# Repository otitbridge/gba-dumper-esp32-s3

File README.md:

# GBAダンパー — バイナリ配布

**導入済みの評価機を受け取った方へ：** [受取後の接続・初回Wi-Fi・ROM／セーブ操作・GBA実機での確認](EVALUATION.md)から始めてください。FW書込みは不要です。機器Wi-Fiの接続情報は譲渡元から個別にお渡しします。

**iPhoneの「ファイル」でROMを取り出し、ファームウェア更新もブラウザから。**
GBAカートリッジのバックアップを、スマホから使いやすく。これから始める人の「入門用の1台目」を目指しています。

- **USBケーブル1本でROMをコピー。** ネイティブUSBに接続すると「GBA-DUMPER」が表示され、iPhoneの「ファイル」やPCから取り出せます。Wi-Fi設定は不要です。
- **Wi-Fiではブラウザから操作。** ROMの読み出し・保存、対応するセーブデータのバックアップ・書込み・元データへの復元ができます。専用アプリのインストールは不要です。
- **更新のためにPCへつなぎ直す手間を減らす。** 初回導入・接続設定後は、ブラウザでGitHubの最新版を確認して更新できます。端末へ保存した署名付き更新ファイルを選ぶ方法にも対応します。
- **更新後の確認と、戻すためのしくみ。** 正規の更新ファイルかを署名で検証し、更新後に起動を確定できなければ旧版へ戻ります。有線書込みによる復旧経路も維持しています。

**ROM 4容量・セーブ5構成で実機検証済み。対応タイトルではWebから自動設定。**

ROMは4／8／16／32 MiB、セーブはEEPROM 512 B／8 KiB、SRAM・FRAM互換32 KiB、Flash 64／128 KiBを確認しています。対応範囲は確認済みタイトル・Rev・チップに限ります。0.25.4は64 KiB Flash対応を含みます。これらは各開発段階の実績で、今回の配布アプリそのものの確認範囲は[検証状況](VALIDATION.md)を参照してください。

[使い方とセーブの復元](USAGE.md) ／ [ファームウェア更新](UPDATE.md) ／ [FW書込み・有線復旧（開発／保守向け）](INSTALL.md)

画像は利用方法を伝える説明用イメージです。[開発の様子をXで見る](https://x.com/ot_it_bridge/status/2111419544761925654)

WeAct ESP32S3-A N16R2と本プロジェクトのGBA用基板V1（20260928）向けの開発版ファームウェアです。
この配布物は **0.25.4 / public build**。ソースコード・最新の設計ファイルは配布しません。GitHubは書込み用バイナリ、操作説明、不具合報告の窓口として使用します。

0.25.4は、Web画面を「USB／Web切替」「ROM読み出し」「セーブ読み書き」「ファームウェア更新」の4タブへ整理しました。Web操作の接続・切断とWi-Fi設定は上部の共通欄にまとめ、Web・Wi-Fi・USBの状態を区別します。タブを移動しても処理と元バックアップを保持し、必要な復元を共通警告で案内します。

前回公開0.22.4から、赤の救助隊国内版B24J Rev0・実物ID D4BFのFlash 64 KiBセーブと自動設定、セーブ対象判定・復元処理の保守整理も含みます。USB MSC・Wi-Fi・署名付きWeb更新を維持します。Web再接続の停滞原因2件を修正し、Macブラウザ30回すべて成功、切断直後の再接続は平均184 msでした。今回の配布アプリ・署名付きOTAそのものを実機確認しています。[確認済み範囲と制限](VALIDATION.md)を確認してください。

0.25.4では空のWebSocket制御フレームの二重受信と、通常HTTPの待機接続による受付枠の占有を修正しました。再接続の成功時平均は約2.8秒から184 msへ短縮しました（同一LANの比較）。

配布FWは公開済みの0.25.4です。今回の追記は検証記録・説明書の更新で、バイナリは変更していません。0.25.4導入済みなら再書込みは不要です。[更新手順](UPDATE.md)を参照してください。

**追加検証（2026-10-28）：** ホスト自動試験34群と、赤の救助隊での通信中断・競合・OTA未確定時の復帰・セーブ復元を確認しました。同一FWの60分継続試験も、50接続・HTTP取得613回で追加エラーなし。iPhoneでの赤の救助隊のROM／セーブ操作はユーザー確認済みです。物理電源断・USB抜去・実スリープなどは追加検証として残します。[対象と確認方法](VALIDATION.md)を参照してください。

## 機器構成

```mermaid
flowchart LR
    CART["GBAカートリッジ"]

    subgraph DUMPER["GBAダンパー"]
        SLOT["カートリッジスロット"]
        ESP["ESP32-S3"]
        USB["USB-C<br/>ROMコピー・給電"]
        WIFI["Wi-Fi<br/>既存APへ接続／設定用AP"]
    end

    PHONE["iPhone<br/>「ファイル」／ブラウザ"]
    PC["PC<br/>ファイル操作／ブラウザ"]

    CART --- SLOT
    SLOT --- ESP
    ESP --- USB
    ESP --- WIFI

    USB <-->|"ROMコピー：どちらか1台"| PHONE
    USB <-->|"ROMコピー：どちらか1台"| PC
    WIFI <-->|"Web操作"| PHONE
    WIFI <-->|"Web操作"| PC
```

## 対応と確認範囲

- ネイティブUSBの読み取り専用「GBA-DUMPER」からROMをコピー。各4 KiBブロックを2回読み、一致したデータを返します。
- Web UIとWi-Fi接続はUSB使用中も維持。カートリッジ操作は排他制御し、WebのUSB停止／有効化ボタンで切り替えます。
- ブラウザからROMの独立2回全量読出し・全バイト照合・保存。USBのブロック照合とは方式が異なります。
- 公式No-Introの登録情報からROM容量を設定。容量は物理測定による判定ではありません。
- 確認済みEEPROM 512 B／8 KiB、キングダムハーツ32 KiB、赤の救助隊64 KiB・ポケモンルビー128 KiB Flashセーブの退避・書込み・元バックアップの復元。Web書込みは独自実機確認済みの設定だけを許可します。
- Wi-Fi接続設定・ESP32親機への自動切替・設定の保存。
- 開発用FWで「シナモン ふわふわ大作戦」4 MiB ROMとEEPROM 512 Bの読み書き・復元を実機確認済み。復元中断→再接続→元セーブ全量2回照合も確認済み。
- 公開用バイナリそのものの確認範囲は[VALIDATION.md](VALIDATION.md)を参照。過去版のiPhone動作報告と今回の公開用アプリそのものの確認を区別しています。
- 0.25.4のiPhone Web操作は赤の救助隊でユーザー確認済みです。取得ファイルの今回のハッシュ照合・機種／iOS詳細・所要時間は未記録。Windows、初期NVSからの設定、0.25.4のUSB全量、処理中の物理USB抜去・スリープ・電源断は未確認です。
- 8 KiB EEPROMはA88J Rev0で元データ書戻し・全量照合済み。SRAM/FRAM互換はB8CJ Rev0の32 KiB、Flash書込みはAXVJ Rev0かつ09C2の128 KiB、B24J Rev0かつD4BFの64 KiBに限定します。一般のSRAM／FRAM／Flash、32 MiB ROMのEEPROMは未対応。ROM容量が登録済みでも、そのタイトルのセーブ書込みまで検証済みという意味ではありません。

## 受取後の操作・FW導入

FW導入済みの評価機は[評価者向け手順](EVALUATION.md)から始めてください。機器自身のWi-Fiへ、譲渡元から個別に渡された接続情報でつなぐだけでWeb操作を始められます。ご自宅のルーターへの登録は必須ではありません。画面ごとの説明は[操作と復元](USAGE.md)を参照してください。

FW未導入の基板への書込み・有線復旧と、譲渡元による接続情報の取得は[INSTALL.md（開発／保守向け）](INSTALL.md)を参照してください。初回のFW導入・有線復旧にはPCを使います。対応基板以外には書き込まないでください。USBでのROMコピーにはWi-Fi設定は不要です。

配布用ビルドには開発者のSSID・Wi-Fiパスワード・OTA認証局を含めません。親機のパスワードは機器内で生成してNVSへ保存します。既存の保存済みWi-Fi設定と親機パスワードは維持されます。
0.14系以降は署名付きファイルをWeb画面から選んで更新できます。0.15系以降は、機器がGitHubから最新版を取得する方式にも対応します。[更新手順](UPDATE.md)。0.13.0からの初回移行と復旧にはUART側USBまたはネイティブUSBのBOOT／RESET書込みモードを使います。UART指令で開始する旧HTTPS方式は無効です。2つのUSBは同時接続しません。Web UIのHTML／JavaScriptと容量一覧は機器からブラウザへ配信され、利用者が閲覧できます。

## 不具合報告

[Issues](https://github.com/otitbridge/gba-dumper-esp32-s3/issues)で受け付けます。バージョン、基板・MCU、端末／ブラウザ、カートリッジ名、再現手順、エラー文を記載してください。
SSID・パスワード・認証トークン・ROM／セーブ本体・個人情報は添付しないでください。報告受付は修正時期や対応範囲の保証ではありません。

<details>
<summary>製品化に一緒に取り組む仲間を募集しています</summary>

利益を得ることより、試作から製品化までの経験を積むことを目的に、基板・筐体・製造検査・販売やサポートを一緒に考えてくれる方を探しています。動作する試作機と評価用バイナリがあります。最新の詳細設計・ソースコードはNDA後に、協業に必要な範囲で共有する予定です。既公開版と第三者素材のライセンス条件は維持します。

</details>

## 配布条件と履歴

自作ソフトウェアはMIT。バイナリにも適用され、表示条件を守った再配布・商用利用を認めます。[ライセンス](LICENSE.md)、[第三者表示](THIRD_PARTY_NOTICES.md)を確認してください。無保証の開発版です。ROM・セーブ本体や取得したヘッダ断片は配布しません。

過去の公開コミットには旧設計と旧ソースがあります。今回の更新は今後の配布内容を変更するもので、既に公開された内容や付与済みの権利を撤回するものではありません。過去版のライセンスは各版の表示に従います。

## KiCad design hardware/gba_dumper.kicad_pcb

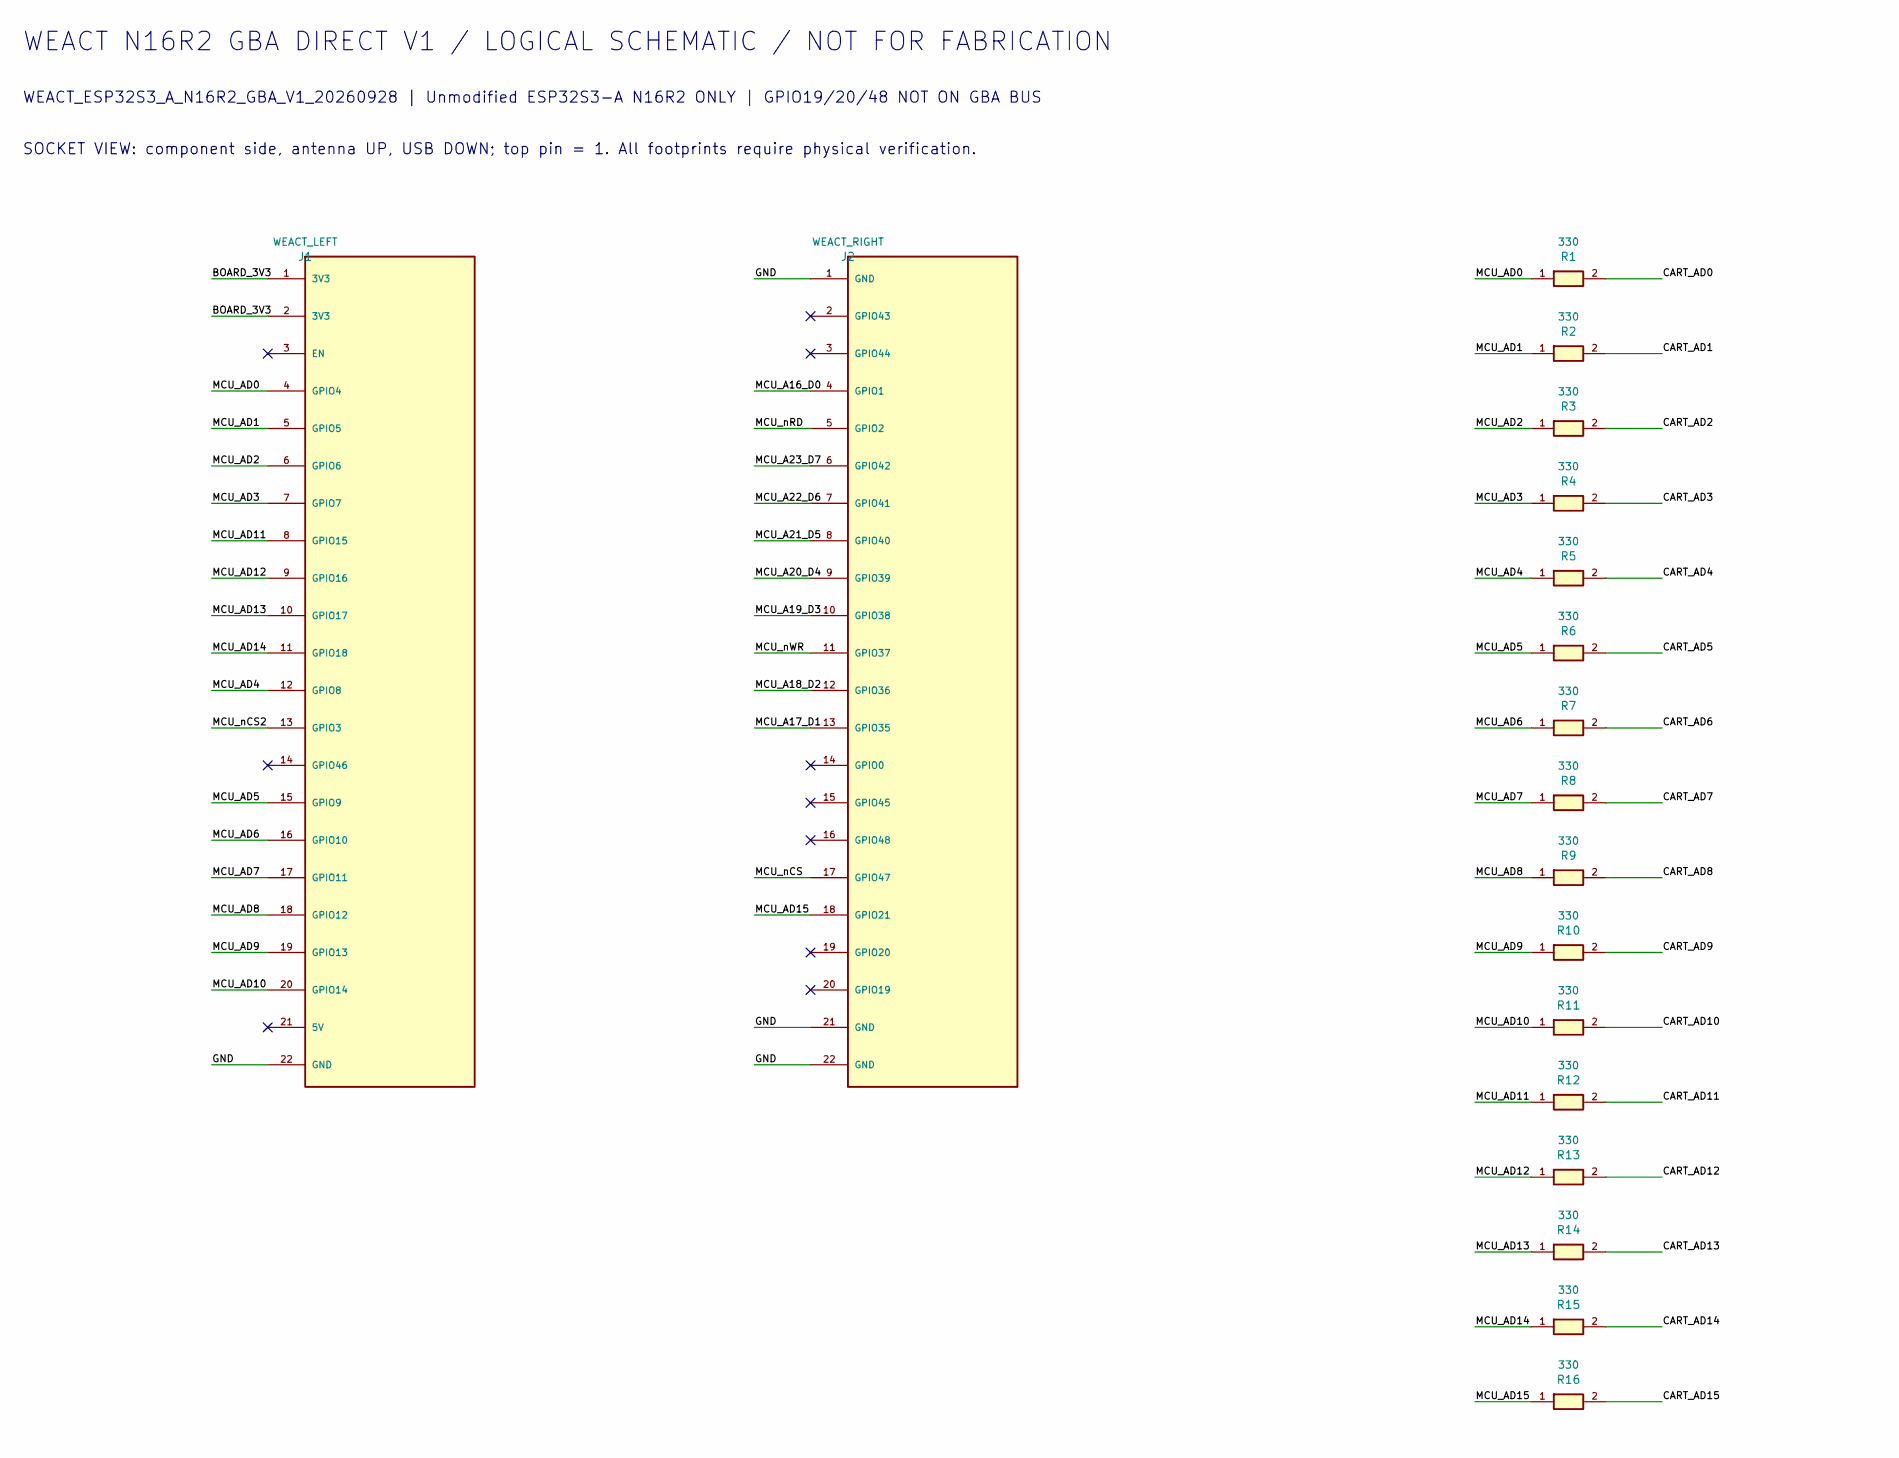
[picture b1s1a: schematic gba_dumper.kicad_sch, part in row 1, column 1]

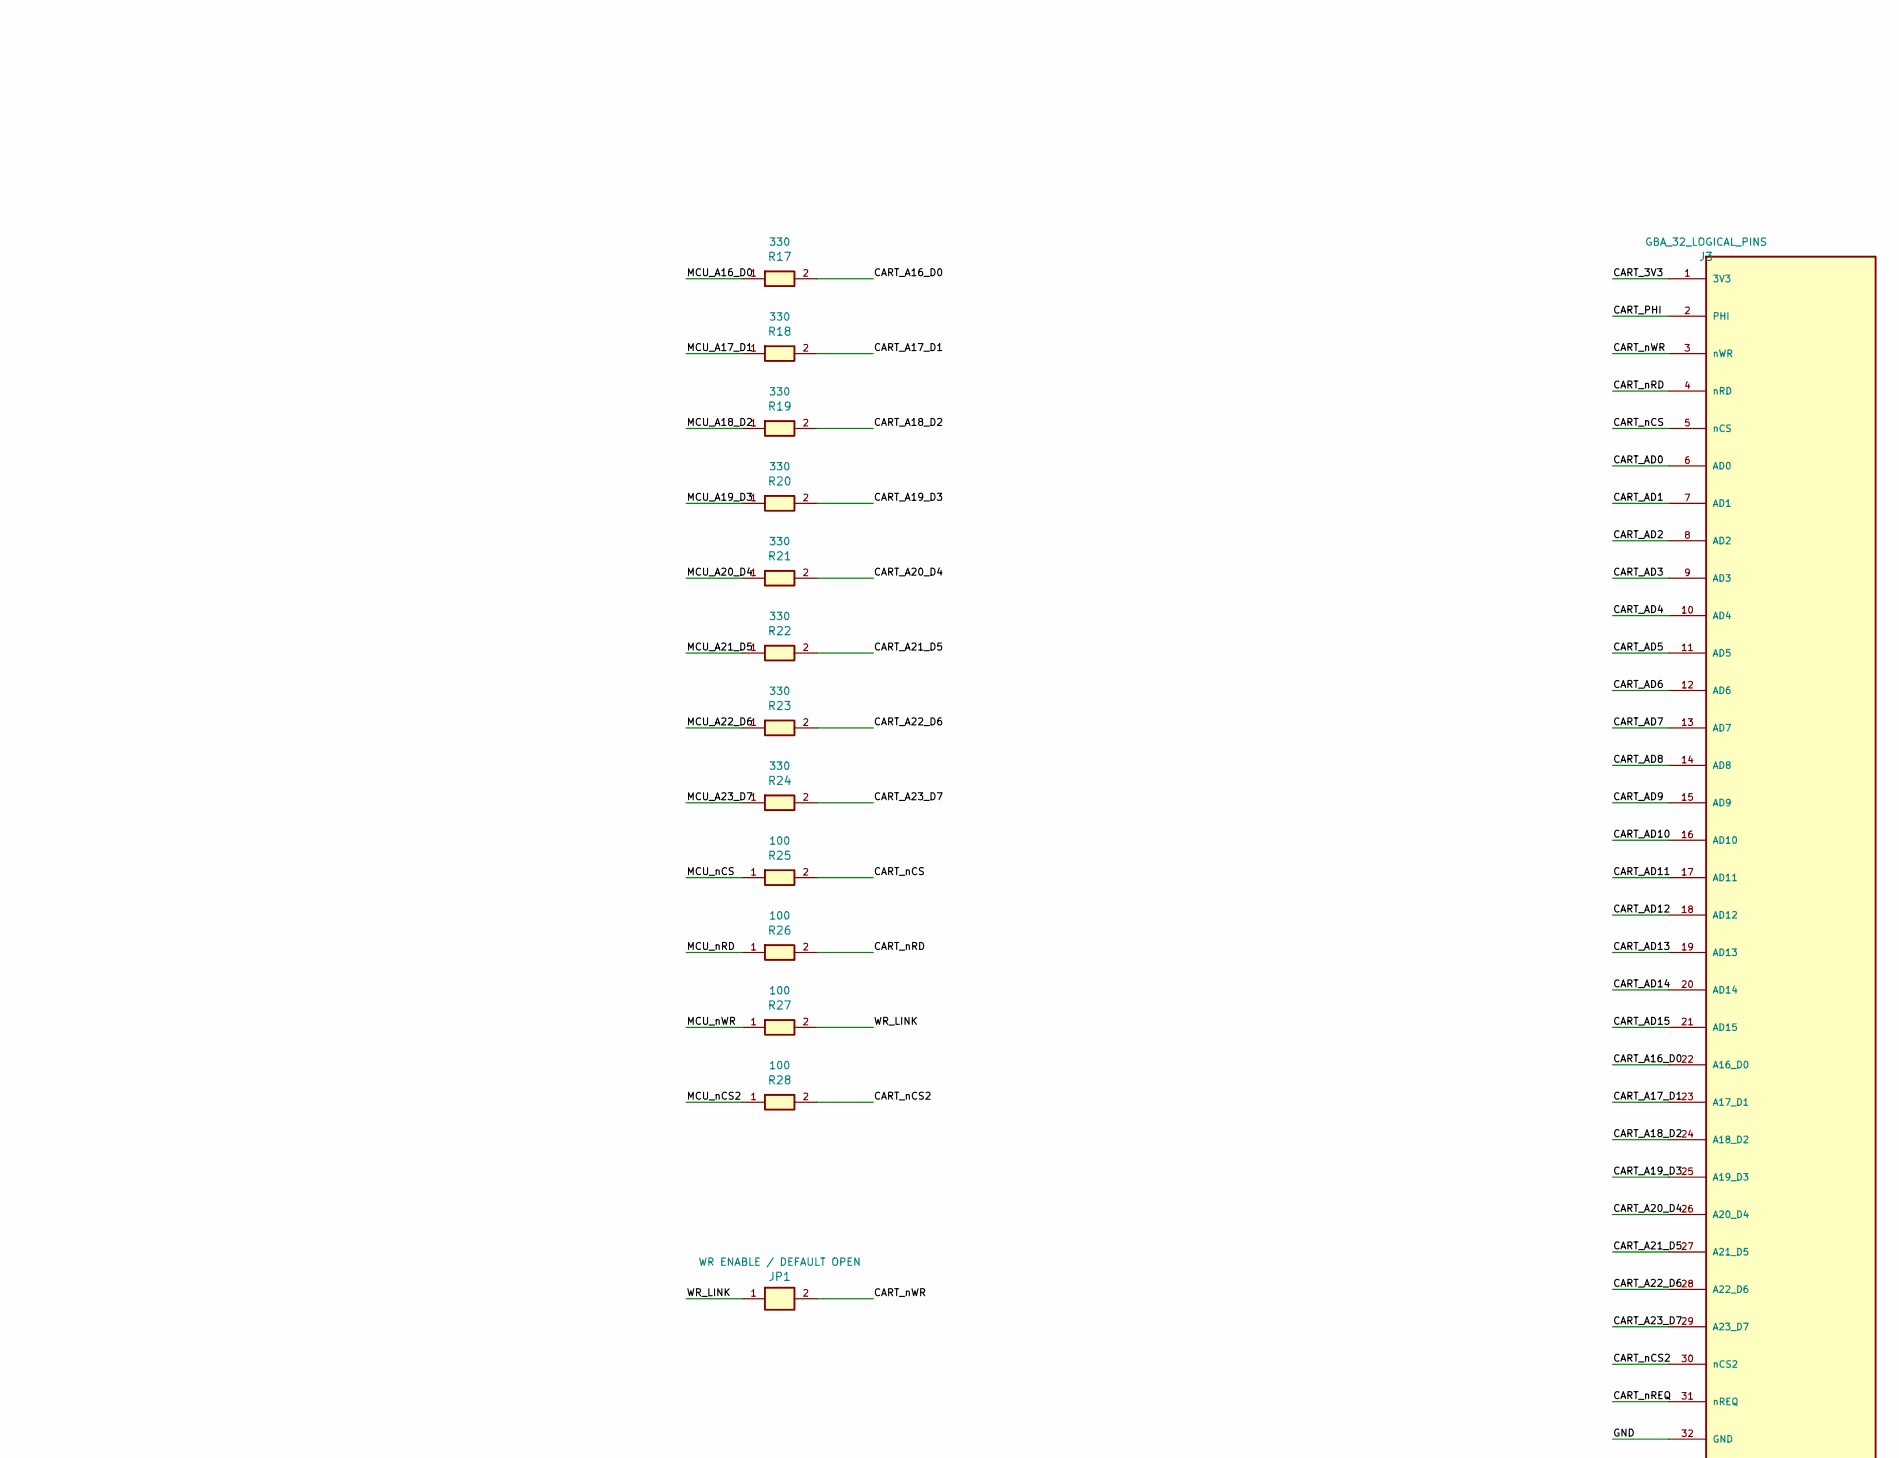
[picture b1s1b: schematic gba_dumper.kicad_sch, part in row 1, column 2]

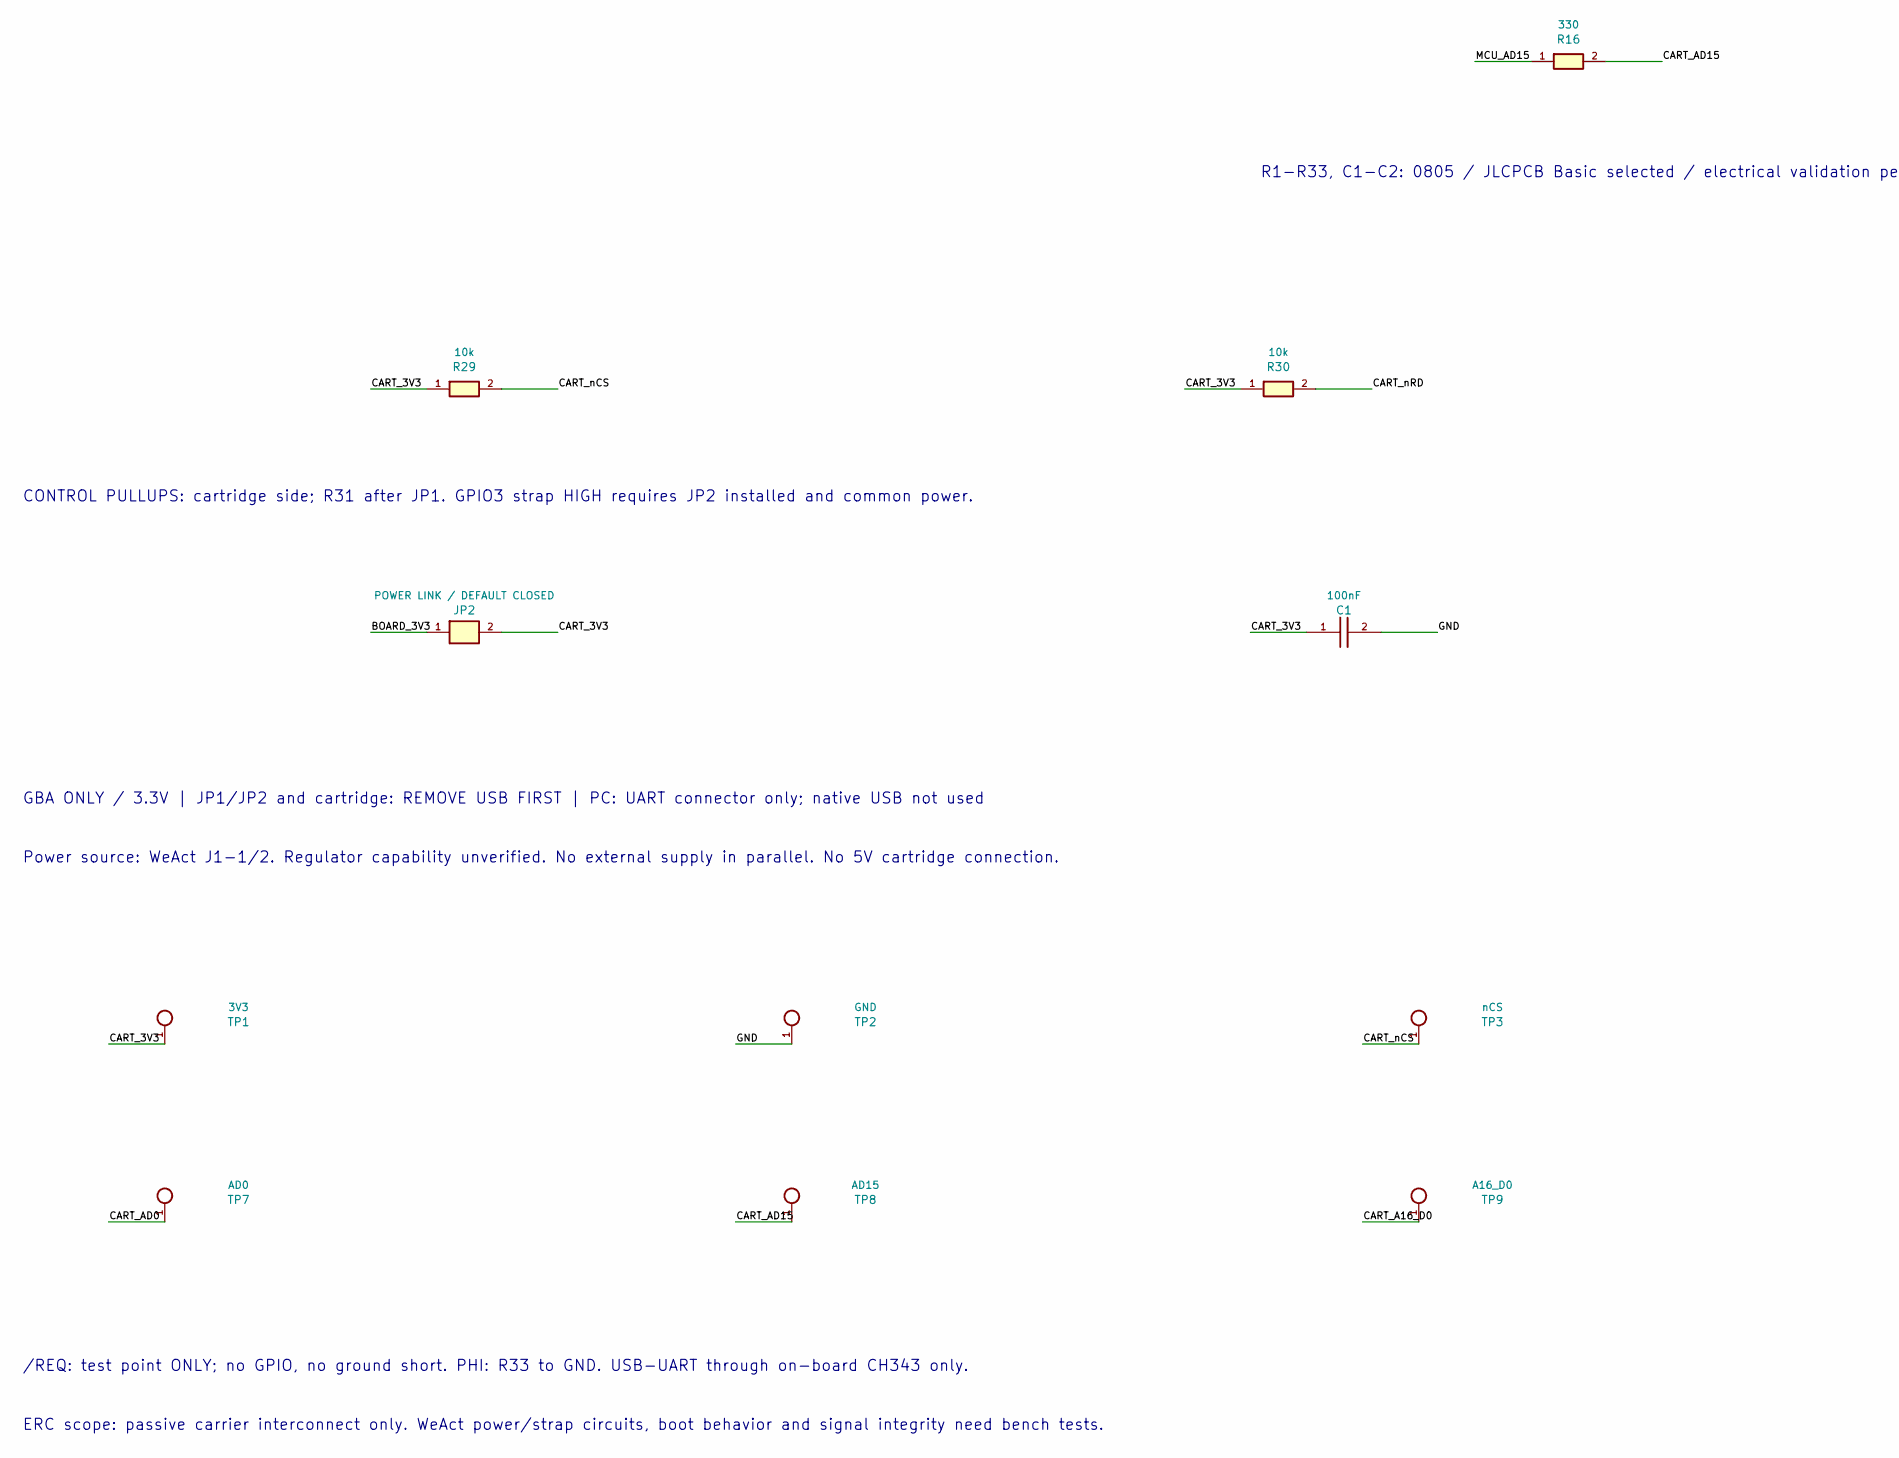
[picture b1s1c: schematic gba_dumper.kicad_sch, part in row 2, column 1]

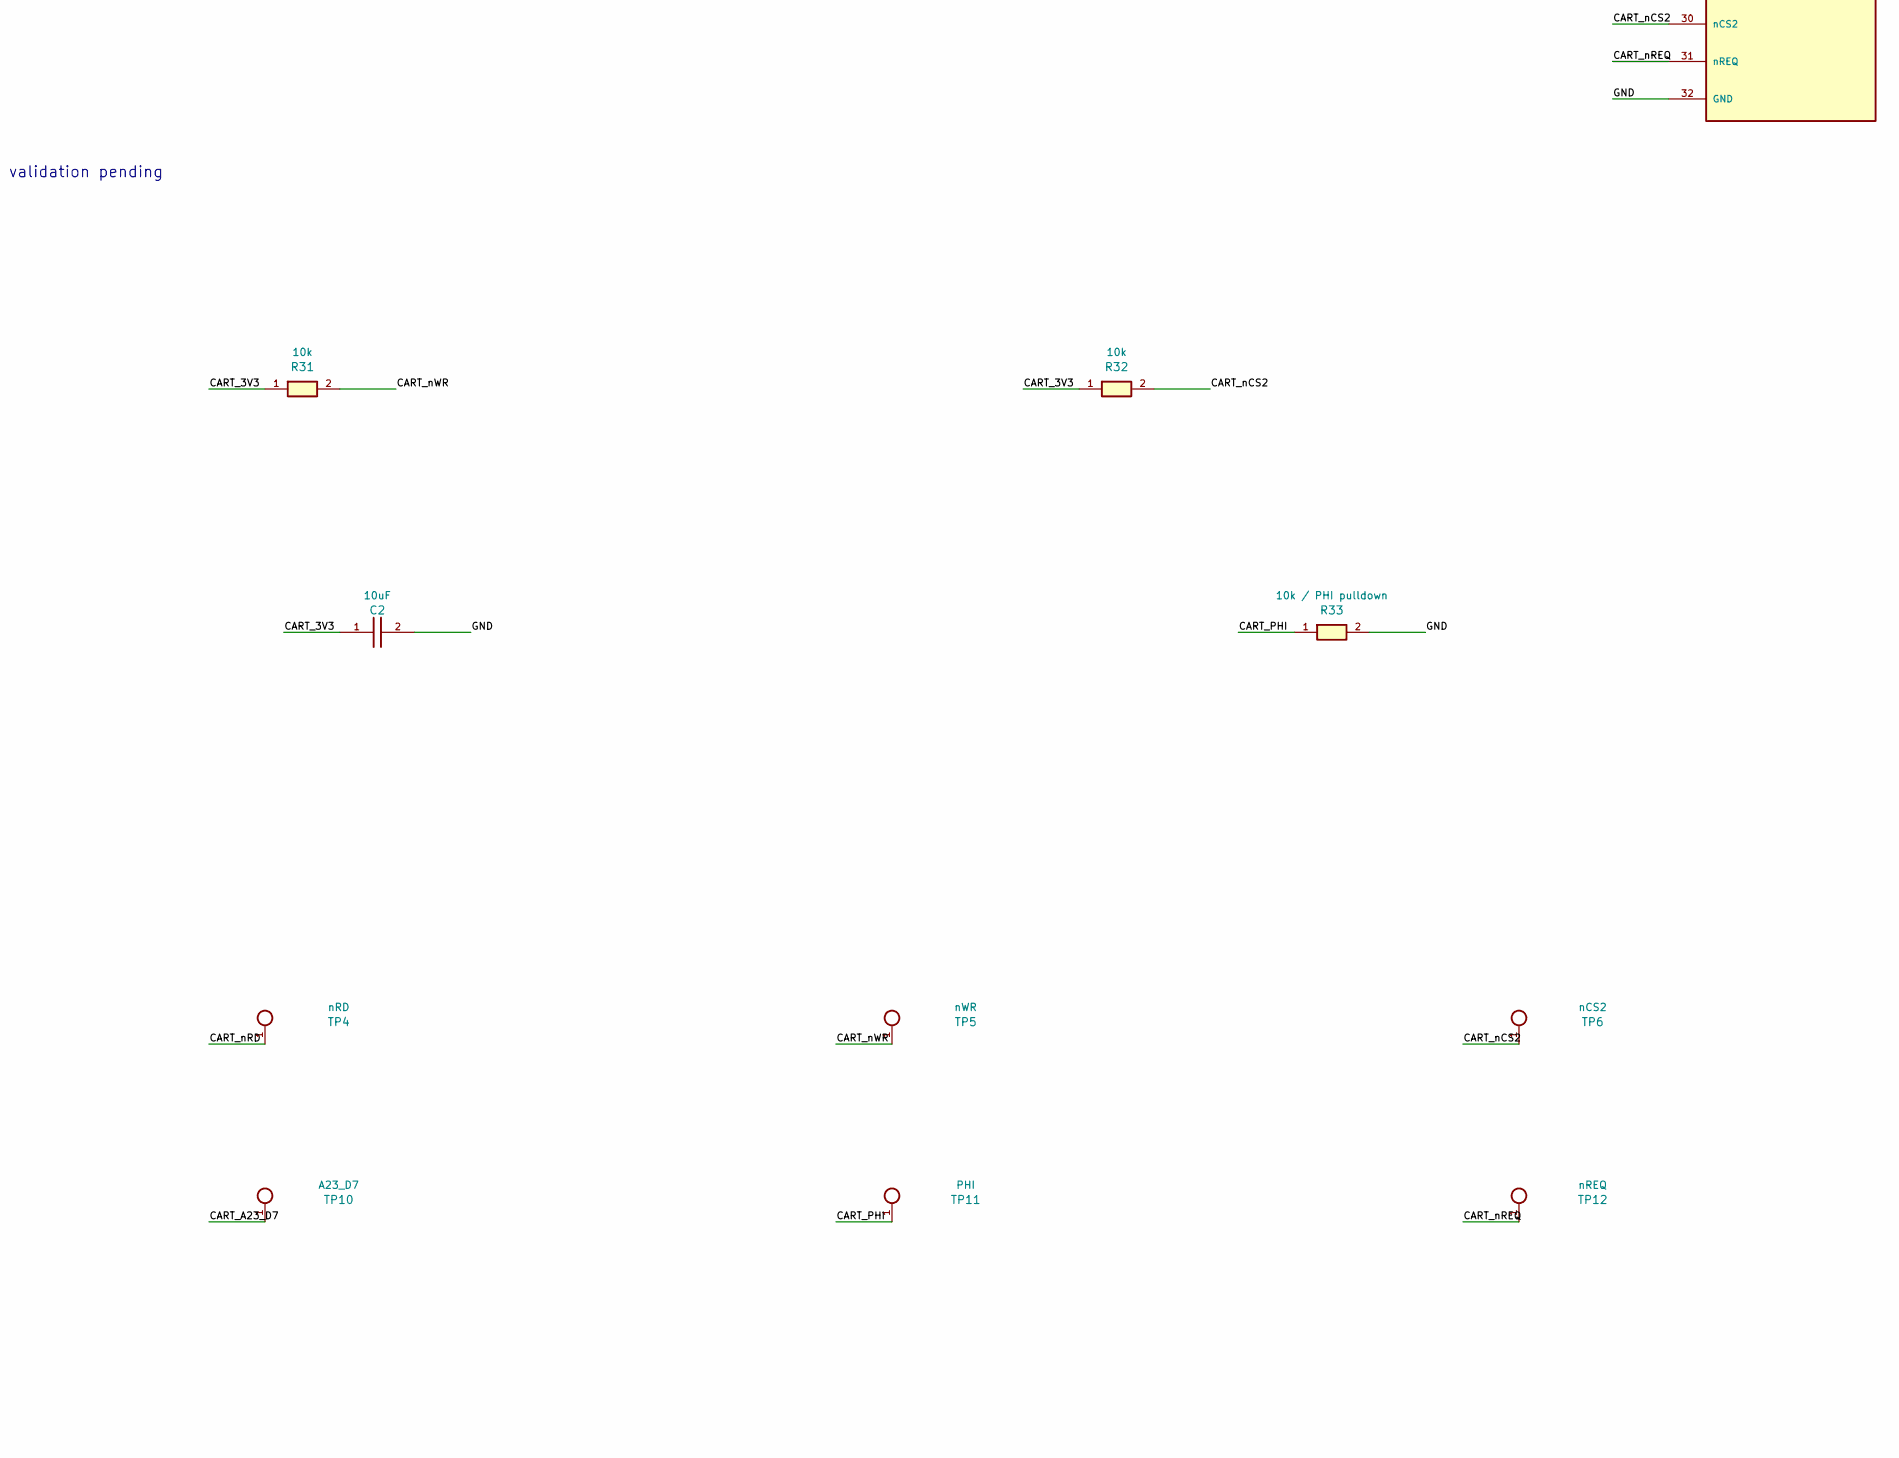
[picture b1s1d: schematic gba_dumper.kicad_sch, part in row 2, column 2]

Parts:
C1: 100nF; C_0805_2012Metric; Rating 50V; X7R; +/-10%; MPN CC0805KRX7R9BB104; LCSC C49678
C2: 10uF; C_0805_2012Metric; Rating 25V; X5R; +/-10%; MPN CL21A106KAYNNNE; LCSC C15850
J1: WEACT_LEFT; PinSocket_1x22_P2.54mm_D1.02mm; Rating 3A; 2.54mm; housing 8.5mm; WeAct header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; MPN FH2.54-40U1GF8.5-0.5
J2: WEACT_RIGHT; PinSocket_1x22_P2.54mm_D1.02mm; Rating 3A; 2.54mm; housing 8.5mm; WeAct header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; MPN FH2.54-40U1GF8.5-0.5
J3: GBA_32_LOGICAL_PINS; GameBoy_Cartridge_AGB_1x32_P1.50mm_Socket_Horizontal; Rating GBA 32 contacts; user-approved footprin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; MPN N/A - manufacturer part number not iden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
JP1: WR ENABLE / DEFAULT OPEN; PinHeader_1x02_P2.54mm_D1.02mm; Rating 3A; 2.54mm pitch; 0.64mm square pins; MPN PH-1X2SG
JP2: POWER LINK / DEFAULT CLOSED; PinHeader_1x02_P2.54mm_D1.02mm; Rating 3A; 2.54mm pitch; 0.64mm square pins; MPN PH-1X2SG
R1, R2, R3, R4, R5, R6, R7, R8, R9, R10, R11, R12, R13, R14, R15, R16, R17, R18, R19, R20, R21, R22, R23, R24: 330; R_0805_2012Metric; Rating 125mW; 150V; +/-1%; +/-100ppm/C; MPN 0805W8F3300T5E; LCSC C17630
R25, R26, R27, R28: 100; R_0805_2012Metric; Rating 125mW; 150V; +/-1%; +/-100ppm/C; MPN 0805W8F1000T5E; LCSC C17408
R29, R30, R31, R32: 10k; R_0805_2012Metric; Rating 125mW; 150V; +/-1%; +/-100ppm/C; MPN 0805W8F1002T5E; LCSC C17414
R33: 10k / PHI pulldown; R_0805_2012Metric; Rating 125mW; 150V; +/-1%; +/-100ppm/C; MPN 0805W8F1002T5E; LCSC C17414
TP1: 3V3; TestPoint_Pad_D2.0mm
TP2: GND; TestPoint_Pad_D2.0mm
TP3: nCS; TestPoint_Pad_D2.0mm
TP4: nRD; TestPoint_Pad_D2.0mm
TP5: nWR; TestPoint_Pad_D2.0mm
TP6: nCS2; TestPoint_Pad_D2.0mm
TP7: AD0; TestPoint_Pad_D2.0mm
TP8: AD15; TestPoint_Pad_D2.0mm
TP9: A16_D0; TestPoint_Pad_D2.0mm
TP10: A23_D7; TestPoint_Pad_D2.0mm
TP11: PHI; TestPoint_Pad_D2.0mm
TP12: nREQ; TestPoint_Pad_D2.0mm

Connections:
/BOARD_3V3: J1.1 (3V3), J1.2 (3V3), JP2.1
/CART_3V3: C1.1, C2.1, J3.1 (3V3), JP2.2, R29.1, R30.1, R31.1, R32.1, TP1.1
/CART_A16_D0: J3.22 (A16_D0), R17.2, TP9.1
/CART_A17_D1: J3.23 (A17_D1), R18.2
/CART_A18_D2: J3.24 (A18_D2), R19.2
/CART_A19_D3: J3.25 (A19_D3), R20.2
/CART_A20_D4: J3.26 (A20_D4), R21.2
/CART_A21_D5: J3.27 (A21_D5), R22.2
/CART_A22_D6: J3.28 (A22_D6), R23.2
/CART_A23_D7: J3.29 (A23_D7), R24.2, TP10.1
/CART_AD0: J3.6 (AD0), R1.2, TP7.1
/CART_AD1: J3.7 (AD1), R2.2
/CART_AD2: J3.8 (AD2), R3.2
/CART_AD3: J3.9 (AD3), R4.2
/CART_AD4: J3.10 (AD4), R5.2
/CART_AD5: J3.11 (AD5), R6.2
/CART_AD6: J3.12 (AD6), R7.2
/CART_AD7: J3.13 (AD7), R8.2
/CART_AD8: J3.14 (AD8), R9.2
/CART_AD9: J3.15 (AD9), R10.2
/CART_AD10: J3.16 (AD10), R11.2
/CART_AD11: J3.17 (AD11), R12.2
/CART_AD12: J3.18 (AD12), R13.2
/CART_AD13: J3.19 (AD13), R14.2
/CART_AD14: J3.20 (AD14), R15.2
/CART_AD15: J3.21 (AD15), R16.2, TP8.1
/CART_PHI: J3.2 (PHI), R33.1, TP11.1
/CART_nCS: J3.5 (nCS), R25.2, R29.2, TP3.1
/CART_nCS2: J3.30 (nCS2), R28.2, R32.2, TP6.1
/CART_nRD: J3.4 (nRD), R26.2, R30.2, TP4.1
/CART_nREQ: J3.31 (nREQ), TP12.1
/CART_nWR: J3.3 (nWR), JP1.2, R31.2, TP5.1
/GND: C1.2, C2.2, J1.22 (GND), J2.1 (GND), J2.21 (GND), J2.22 (GND), J3.32 (GND), R33.2, TP2.1
/MCU_A16_D0: J2.4 (GPIO1), R17.1
/MCU_A17_D1: J2.13 (GPIO35), R18.1
/MCU_A18_D2: J2.12 (GPIO36), R19.1
/MCU_A19_D3: J2.10 (GPIO38), R20.1
/MCU_A20_D4: J2.9 (GPIO39), R21.1
/MCU_A21_D5: J2.8 (GPIO40), R22.1
/MCU_A22_D6: J2.7 (GPIO41), R23.1
/MCU_A23_D7: J2.6 (GPIO42), R24.1
/MCU_AD0: J1.4 (GPIO4), R1.1
/MCU_AD1: J1.5 (GPIO5), R2.1
/MCU_AD2: J1.6 (GPIO6), R3.1
/MCU_AD3: J1.7 (GPIO7), R4.1
/MCU_AD4: J1.12 (GPIO8), R5.1
/MCU_AD5: J1.15 (GPIO9), R6.1
/MCU_AD6: J1.16 (GPIO10), R7.1
/MCU_AD7: J1.17 (GPIO11), R8.1
/MCU_AD8: J1.18 (GPIO12), R9.1
/MCU_AD9: J1.19 (GPIO13), R10.1
/MCU_AD10: J1.20 (GPIO14), R11.1
/MCU_AD11: J1.8 (GPIO15), R12.1
/MCU_AD12: J1.9 (GPIO16), R13.1
/MCU_AD13: J1.10 (GPIO17), R14.1
/MCU_AD14: J1.11 (GPIO18), R15.1
/MCU_AD15: J2.18 (GPIO21), R16.1
/MCU_nCS: J2.17 (GPIO47), R25.1
/MCU_nCS2: J1.13 (GPIO3), R28.1
/MCU_nRD: J2.5 (GPIO2), R26.1
/MCU_nWR: J2.11 (GPIO37), R27.1
/WR_LINK: JP1.1, R27.2

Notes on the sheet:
WEACT N16R2 GBA DIRECT V1 / LOGICAL SCHEMATIC / NOT FOR FABRICATION
WEACT_ESP32S3_A_N16R2_GBA_V1_20260928 | Unmodified ESP32S3-A N16R2 ONLY | GPIO19/20/48 NOT ON GBA BUS
SOCKET VIEW: component side, antenna UP, USB DOWN; top pin = 1. All footprints require physical verification.
R1-R33, C1-C2: 0805 / JLCPCB Basic selected / electrical validation pending
CONTROL PULLUPS: cartridge side; R31 after JP1. GPIO3 strap HIGH requires JP2 installed and common power.
GBA ONLY / 3.3V | JP1/JP2 and cartridge: REMOVE USB FIRST | PC: UART connector only; native USB not used
Power source: WeAct J1-1/2. Regulator capability unverified. No external supply in parallel. No 5V cartridge connection.
/REQ: test point ONLY; no GPIO, no ground short. PHI: R33 to GND. USB-UART through on-board CH343 only.
ERC scope: passive carrier interconnect only. WeAct power/strap circuits, boot behavior and signal integrity need bench tests.

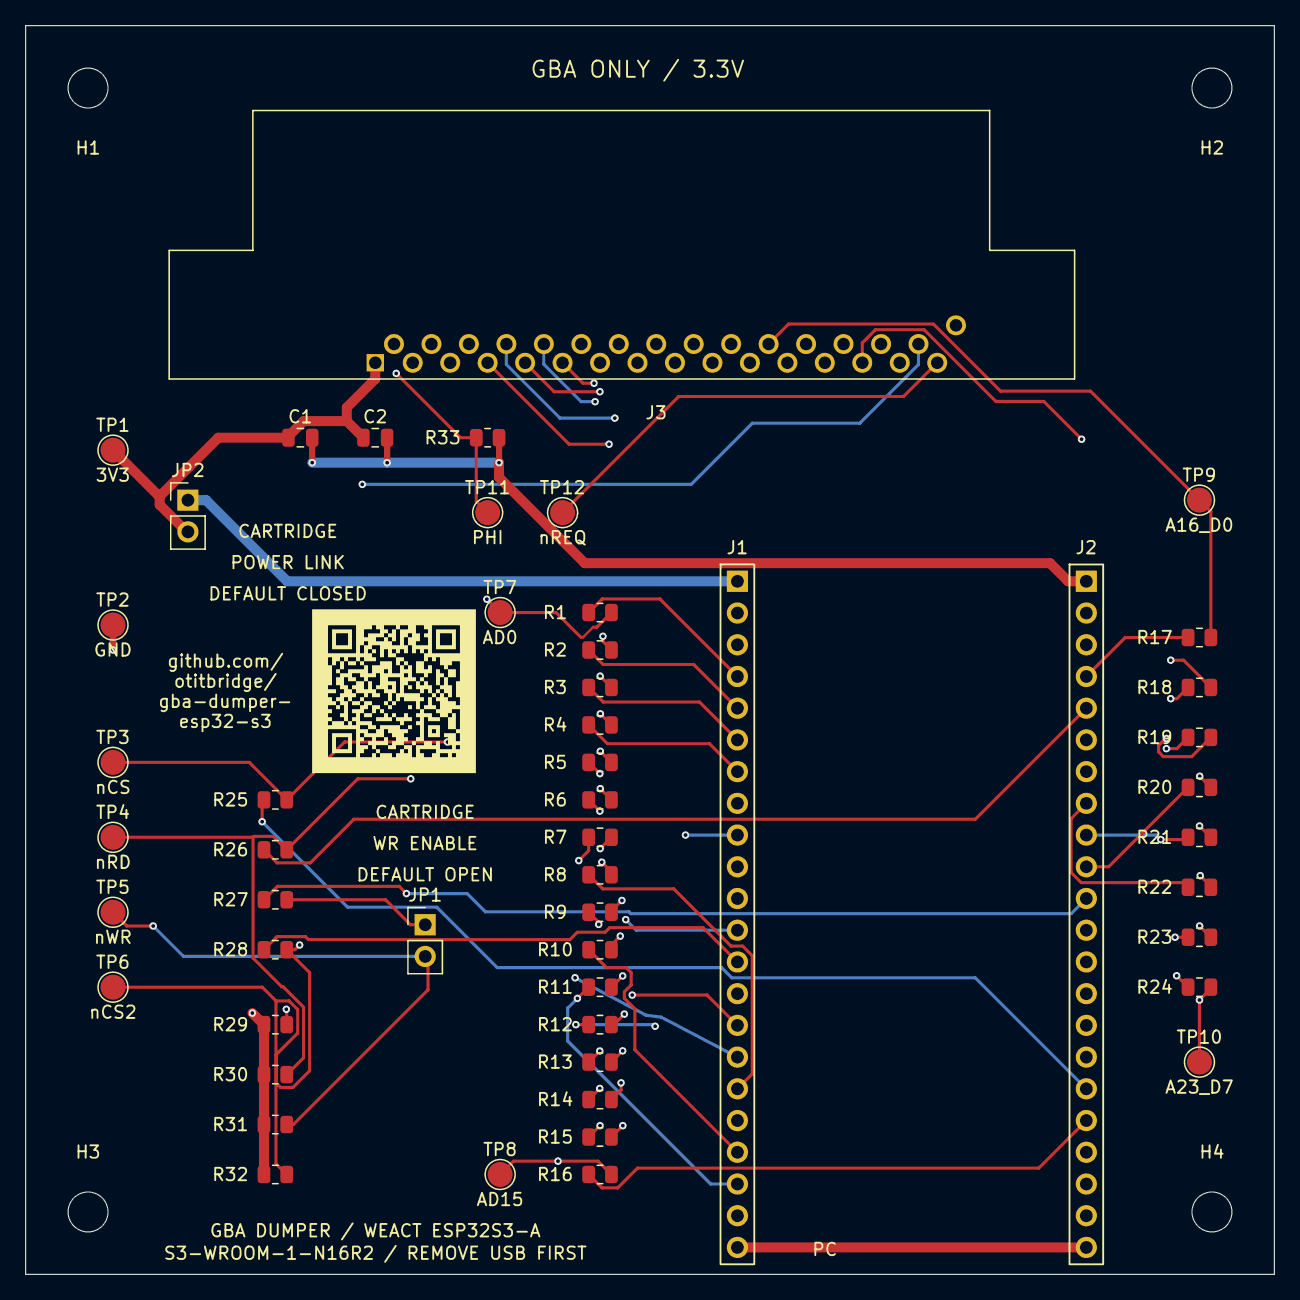
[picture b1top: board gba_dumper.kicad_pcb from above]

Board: 4 copper layers, 100.0 x 100.0 mm, 56 parts (0 on the bottom side), 62 nets.

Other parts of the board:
H1, H2, H3, H4: M3 / 14mm foot; MountingHole_3.2mm_M3
